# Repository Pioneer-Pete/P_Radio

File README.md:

## Introduciton

P_Radio was created as a homage to the iconic radios seen in the Portal video game series, to be distributed around UW-Platteville on April 1st, 2025.
The project's goal was to create an accurate representation of the Portal radios, both in appearance and sound, while retaining a sub-dollar cost per unit to enable a large number of units to be created and distributed.
Excluding the 3D printing costs, each unit meets the original goal, coming in at exactly $1. Filament costs ended up being approximately $0.40 per unit.

## Project Information

 3D Models: The base and shell were modeled in Fusion 360. STEP, STL, and F3D files are included.
 
 PCB Design: A custom PCB was designed using KiCAD, and four expansion ports were included for any future tinkerers out there.
 
 Code: The radio is powered by an STM8S003F3, a cost-effective 8-bit microcontroller. This necessitated using STM's STVD and STVP to program the boards. If remaking the project, I would look into using the STM Arduino library instead.

 Assembly: Everything snaps together without any hardware; the hole at the top of the shell accepts a ~4-inch length of standard 1.75mm filament to act as the "antenna". The batteries require a small strip of aluminum foil to complete the circuit at the end opposite the PCB. The calculated battery lifespan is 1-2 months, but it has yet to be tested.

## Fine Print

This is a non-commercial, personal project created for an April Fools' joke at the UW-Platteville campus. All copyrightable content (such as the Aperture Science logo) is the property of its respective owners and is used here for parody purposes only.

Feel free to use and modify the project as you like for fun, but please do not distribute any copyrighted content (logos, names) for commercial purposes.

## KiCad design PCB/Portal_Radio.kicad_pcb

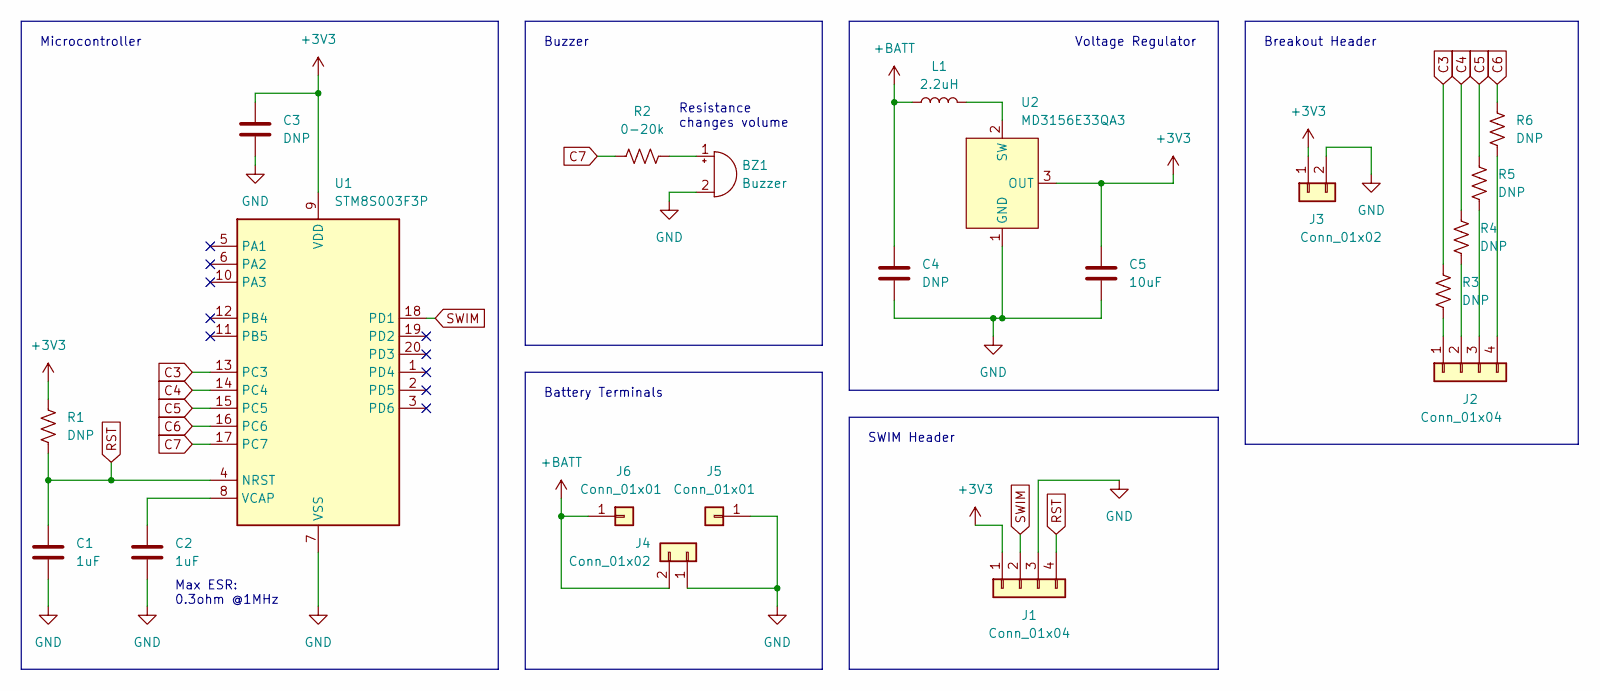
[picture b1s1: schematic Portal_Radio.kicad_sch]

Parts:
BZ1: Buzzer; MagneticBuzzer_ProSignal_ABT-410-RC
C1, C2: 1uF; C_0603_1608Metric
C3, C4: DNP; C_0603_1608Metric
C5: 10uF; C_0603_1608Metric
J1, J2: Conn_01x04; PinHeader_1x04_P2.54mm_Vertical
J3, J4: Conn_01x02; PinHeader_1x02_P2.54mm_Vertical
J5, J6: Conn_01x01; AA_Battery
L1: 2.2uH; L_0603_1608Metric
R1, R3, R4, R5, R6: DNP; R_0603_1608Metric
R2: 0-20k; R_0603_1608Metric
U1: STM8S003F3P; TSSOP-20_4.4x6.5mm_P0.65mm
U2: MD3156E33QA3; SOT-23-3

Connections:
+3V3: C3.1, C5.1, J1.1, J3.1, R1.1, U1.9 (VDD), U2.3 (OUT)
+BATT: C4.1, J4.2, J6.1, L1.1
C3: R3.1, U1.13 (PC3)
C4: R4.1, U1.14 (PC4)
C5: R5.1, U1.15 (PC5)
C6: R6.1, U1.16 (PC6)
C7: R2.1, U1.17 (PC7)
GND: BZ1.2 (-), C1.2, C2.2, C3.2, C4.2, C5.2, J1.3, J3.2, J4.1, J5.1, U1.7 (VSS), U2.1 (GND)
unnamed: BZ1.1 (+), R2.2
unnamed: J2.1, R3.2
unnamed: J2.2, R4.2
unnamed: J2.3, R5.2
unnamed: J2.4, R6.2
unnamed: C2.1, U1.8 (VCAP)
unnamed: L1.2, U2.2 (SW)
RST: C1.1, J1.4, R1.2, U1.4 (NRST)
SWIM: J1.2, U1.18 (PD1)

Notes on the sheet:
Resistance changes volume
Buzzer
Breakout Header
Voltage Regulator
Battery Terminals
Max ESR: 0.3ohm @1MHz
SWIM Header
Microcontroller

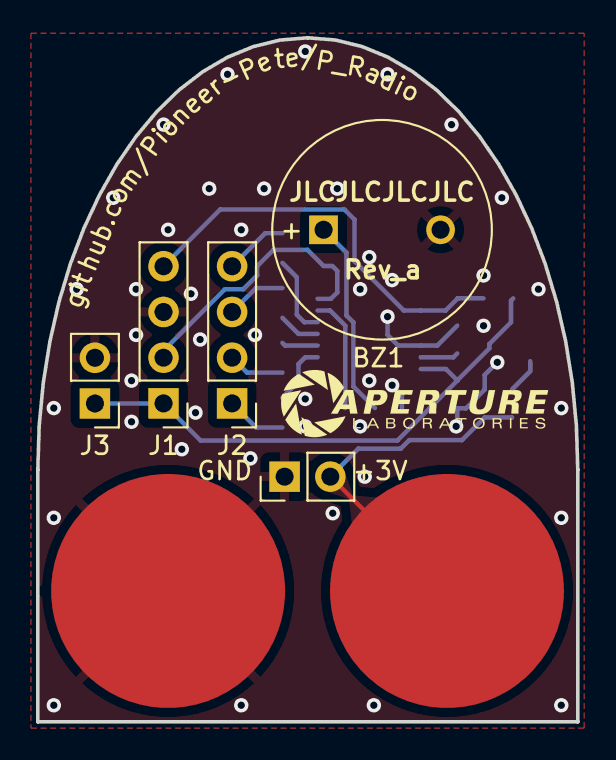
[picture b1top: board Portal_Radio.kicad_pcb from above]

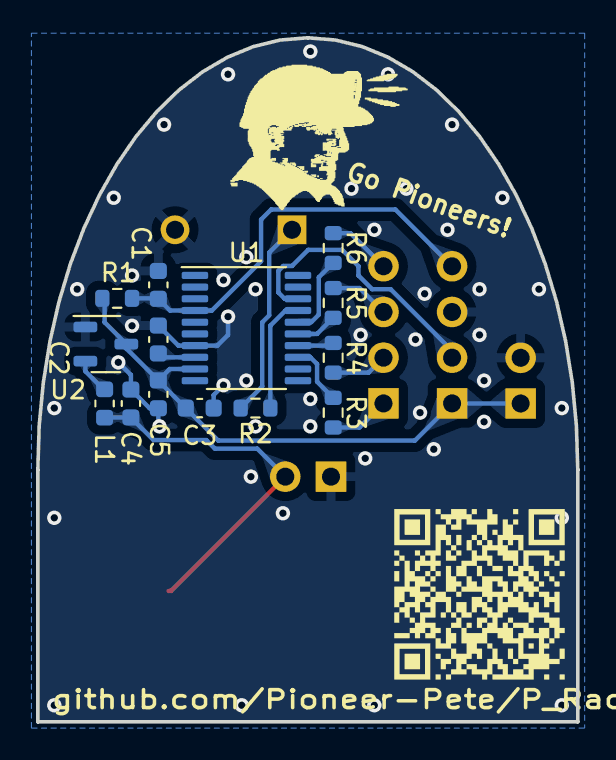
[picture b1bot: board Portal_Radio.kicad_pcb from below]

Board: 2 copper layers, 30.0 x 38.0 mm, 21 parts (14 on the bottom side), 17 nets.

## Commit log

2025-03-24 Removed file
2025-03-27 Add main.c and main.h
